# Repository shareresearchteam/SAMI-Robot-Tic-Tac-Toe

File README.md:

# Social Animated Mechanical Interlocutor (SAMI) Robot
The Social Animated Mechanical Interlocutor (SAMI) robot is based on the [Aster](https://www.thingiverse.com/thing:3992150) robot, which is a modified [Poppy](https://www.thingiverse.com/thing:2280067) robot that used MG996R servo motors instead of the much more expensive dynamixels. The SAMI robot has been modified to use the HiWonder HTS serial bus servo motor series in addition to implementing additional features.

## High Level System Capabilities

### Robot
Serial USB connection to PC to send expressions/joint movement commands
Capabilities & DoF:
 1. 8x8 LED matrix eyes, with a bunch of premade expressions (but, as previously mentioned, you can send custom ones, or swap out the eyes entirely
 2. 3 DoF in neck for pan, forward tilt, and side tilt
 3. 2 DoF in chest for forward-backward and side-side lean
 4. 4 DoF for arm (two for the shoulder, one in bicep for arm rotation, one in elbow)
 5. Single tendon gripper for open/close hand (or easy swap in for static or other hand)
 6. 3 DoF for legs (one each hip, knee, ankle)
 7. Mr. Potato Head style swappable headshell parts

### Sensor Box
Serial USB connection sends messages to PC about:
 - Button presses
 - Person presence/movement (ultrasonic + PIR, we’re still fiddling with calibration, but basically to register is someone walks by or comes up to the system)
 - RFID (for specific participant recognition)

### Captions/Speakers/Video/Microphone
Captions are a mini monitor hooked up to the computer, speakers, video and microphone are a webcam or whatever hardware connected to a PC.

### Utilities/etc:
 - JSON-structured animation/behavior/interaction authoring
 - Planning to make some C libraries (with python and c# wrappers) for things like handling serial communication and running the JSON animations/etc
 - Premade eye expressions
 - Premade robot animations/behaviors

## Assembly

## Operation
High level command and operation is managed on a computer system, 
Low level communication with the robot is performed via serial over USB, using the communication packet architecture presented below. 

### Serial Communication Packet Architecture
Each serial packet sent or recieved includes static starting and ending bytes to denote when a packet is complete, and the content between these bytes is our message.
 - Packet start byte char: <
 - Packet end byte char: >

Each message begins with a message topic, which is a single char byte defining the type and structure of content the rest of the message will include. The robot uses one set of message topics, and the sensor box uses a different set of message topics.

The list of existing robot message topics is:
 - J - [Joint Message]()
 - E - [Emote Message]()
 - P - [Power Message]()

The list of existing sensor box message topics is:
 - B - [Button Message]()

These existing message types, corresponding message topics, and remaining content structure are each presented individually below.

#### Joint Message
Joint messages are defined with the message topic byte 'J', followed by the time it should take for the joints to reach the requested position (in seconds) followed then by a list of paired bytes that denote the joint servo id, and the angle

So, a message telling two servos, with ids 1 and 5 to go to 90 degrees in 2 seconds would be 8 bytes and look like:
   <J2190590>

The maximum length of a joint message, if you set all motors, would be:
   start byte + message type + time + (jointID * number of motors) + (jointID * number of motors) + stop byte

For the standard system, which has 21 motors, this would be 46 bytes maximum.

#### Emote Message
Emote messages are defined with the message topic byte 'E', followed by the id for the emote they want to display, as ordered by the NeoEyes library.

So neutral expression would be 4 bytes and look like: <E0>

#### Power Message
Power messages tell us whether to turn the relays on or off, and which relays. We can also send back power messages to the PC if the Arduino automatically cuts a relay because of a motor going over temperature.

Power messages are defined with the message topic byte 'P', followed by a 1 (on) or 0 (off), and which relays to turn on. The relay markers are:
 - T - Neck and torso motor control
 - A - Arms motor control
 - L - Legs motor control
 - E - Everything, aka all of the relays.

The power message is 5, 6, or 7 bytes. A message saying to turn on power to the neck and torso would look like:
   <P1T>

If you wanted to turn off all relays, you could do so either by sending 'E': 
   <P0E>

Or by sending 'TAL' (order invariant, so TLA, ATL, ALT, LTA, or LAT are all acceptable options).
   <P0TAL>

#### Button Message
Button messages send a single integer value corresponding the 0, 1, or 2, which in turn are the first, second, or third button on the sensor box being pressed, beginning from the left hand side when facing towards the front of the box.

## Components/Packages/How TF do I organize this???
Mechanical
Electrical
Arduino Code
C Libraries
JSON behavior files
Audio files + caption text
C# testing/development UI
3D model files
URDF model

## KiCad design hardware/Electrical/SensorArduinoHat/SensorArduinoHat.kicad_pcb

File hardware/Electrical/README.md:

# Aaron Robot Electrical
All of the information for the electrical systems and wiring for the robot.

## Future Improvements
TODO:
 - So much assembly

## Cable Fabrication
There are three power cables that need to be assembled to supply power to the robot. The components and assembly instructions for each are provided below.

For the fork connectors we used [14-16 gauge, #8 fork connectors with heat shrink attached, from wirefy](https://www.amazon.com/dp/B07YBHDBST) and for the spade connectors, we used [10-12 guage, female quick disconnect spade connectors with heat shrink, also from wirefy](https://www.amazon.com/dp/B08BP57G94).

### 12V PCB to Power Supply
This cable assembly connects the 12V power on the motor control PCB to the 12V power supply for the robot.

#### Materials
 - 1x red 14AWG braided wire, 18" length minimum
 - 2x red heat shrink pieces
 - 1x black 14AWG braided wire, 18" length minimum
 - 2x black heat shrink pieces
 - 1x XT-60 female plug
 - 2x fork connector #8, 16-14 gauge opening

#### Assembly
For connecting the wires to the XT-60 connector, you may follow [this](https://www.youtube.com/watch?v=eeDYUymM3XI) short video tutorial.

### 5V PCB to Power Supply
This cable assembly connects the 5V power on the motor control PCB to the 5V power supply for the robot.

#### Materials
 - 1x red 18AWG braided wire, 24" length minimum
 - 2x red heat shrink pieces
 - 1x black 18AWG braided wire, 24" length minimum
 - 2x black heat shrink pieces
 - 1x XT-30 female plug
 - 2x fork connector #8, 22-16 gauge opening

#### Assembly

### 12V Power Supply to Outlet to 5V Power Supply
This cable assembly connects both the 12V power supply and 5V power supply to the power outlet on the back of the chair that takes 120VAC wall power. The 12V supply and 5V supply are at different locations and could use different cable lengths, but for ease of assembly, we use the same lengths of wire for both of them.

#### Materials
 - 2x red 14AWG braided wire, 12" length minimum
 - 3x red heat shrink pieces
 - 2x black 14AWG braided wire, 12" length minimum
 - 3x black heat shrink pieces
 - 2x yellow 14AWG braided wire, 12" length minimum
 - 3x yellow heat shrink pieces
 - 6x fork connector #8, 16-14 gauge opening
 - 3x female spade connector, 12-10 gauge opening

#### Assembly

### Hip Motor to Control PCB JST Cable
For the two motors in the hips, the JST cables that come with the motors will need to be lengthened to reach the motor pcb. You'll need to splice in a 12" length of wire. This can be done by soldering, or with mechanical splice connectors such as [these](https://www.amazon.com/dp/B0DGLJJRZ5).

#### Materials
 - 1x 3 pin JST cable (comes with motor)
 - 1x 3 wire cable, 12" length minimum
 - Solder and heat shrink or [2x mechanical crimp splicers](https://www.amazon.com/dp/B0DGLJJRZ5).

#### Assembly

### Eye Panel Short Cable
This is the short cable combining the two LED array panels for the eyes.

#### Materials
 - 2x 3pin JST XH2.54 connectors
 - 1x 3 wire cable, 4" length (try not to go long)

#### Assembly

### Eye Panel Long Cable
 - 1x 3pin JST XH2.54 connector
 - 1x 3pin JST PH2.0 connector
 - 1x 3 wire cable, ?? length minimum

#### Materials

#### Assembly

### Gripper Cable

#### Materials
 - 1x 3pin JST PH2.0 connector
 - 1x 3pin Dupont female connector
 - 1x 3 wire cable, ?? length minimum

#### Assembly

## Bill of Materials
Currently all in the excel doc one level up

 - Power Supply: 12V, 30A, buck converter down to 6V (Need to check current still)
 - PTC Fuses for each motor: RKEF075-2
 - Relays for each motor group: PR9-5V-200-1A
 - NPN Transistors for each motor group relay controller: BC547CBU-ND
 - Diode between motors and servo: 15SQ100

## Wiring Guide

## Custom PCBs

### Safety Circuitry

#### Motor Current Characteristics

See the motor current characteristics for the arms (without gripper) and legs below. The measured torso nod motor current during operation was seen as a maximum of 0.6A, and the stall current was measured at 1.12A. The measured torso tilt current during operation similarly hit a maximum of 0.6A, but the stall current when held still was 1.99A.

#### Safety Circuit Current Breakdown
We have PTC fuses to protect the servos from melting themselves, and 15A relays so we can cut power to the servos if operation is not currently necessary.

##### Relay Circuits
There are 6 relay groups, broken down for each arm, and leg, as well as the neck and torso. Each relay needs 40mA control current, which becomes 240mA current from the Arduino 5V line. To turn the control circuit on and off, each relay has an individual NPN transistor. These transistors are controlled by a common Arduino pin.

 - Arm Motors: Max Rating: 12.5A, 75W @ 6VDC
    - Chest Shoulder
    - Shoulder
    - Arm Twist
    - Elbow
    - Single Tendon Gripper
 - Leg Motors: Max Rating: 7.5A, 45W @ 6VDC
    - Hip
    - Knee
    - Ankle
    - Hip flexor motor? (add another 2.5A)
 - Head Motors: Max Rating: 7.5A, 45W @ 6VDC
    - Head Twist
    - Head Nod
    - Head Tilt
    - Camera pan motor? (add another 2.5A)
 - Torso Motors: Max Rating: ~6A, 45W @ 7.4VDC
    - Torso Tilt
    - Torso Bow
    - Spine-hip bow point? (adds another ~3A)

## References
 - [Flyback diode example circuit](https://blog.mbedded.ninja/electronics/components/relays/)

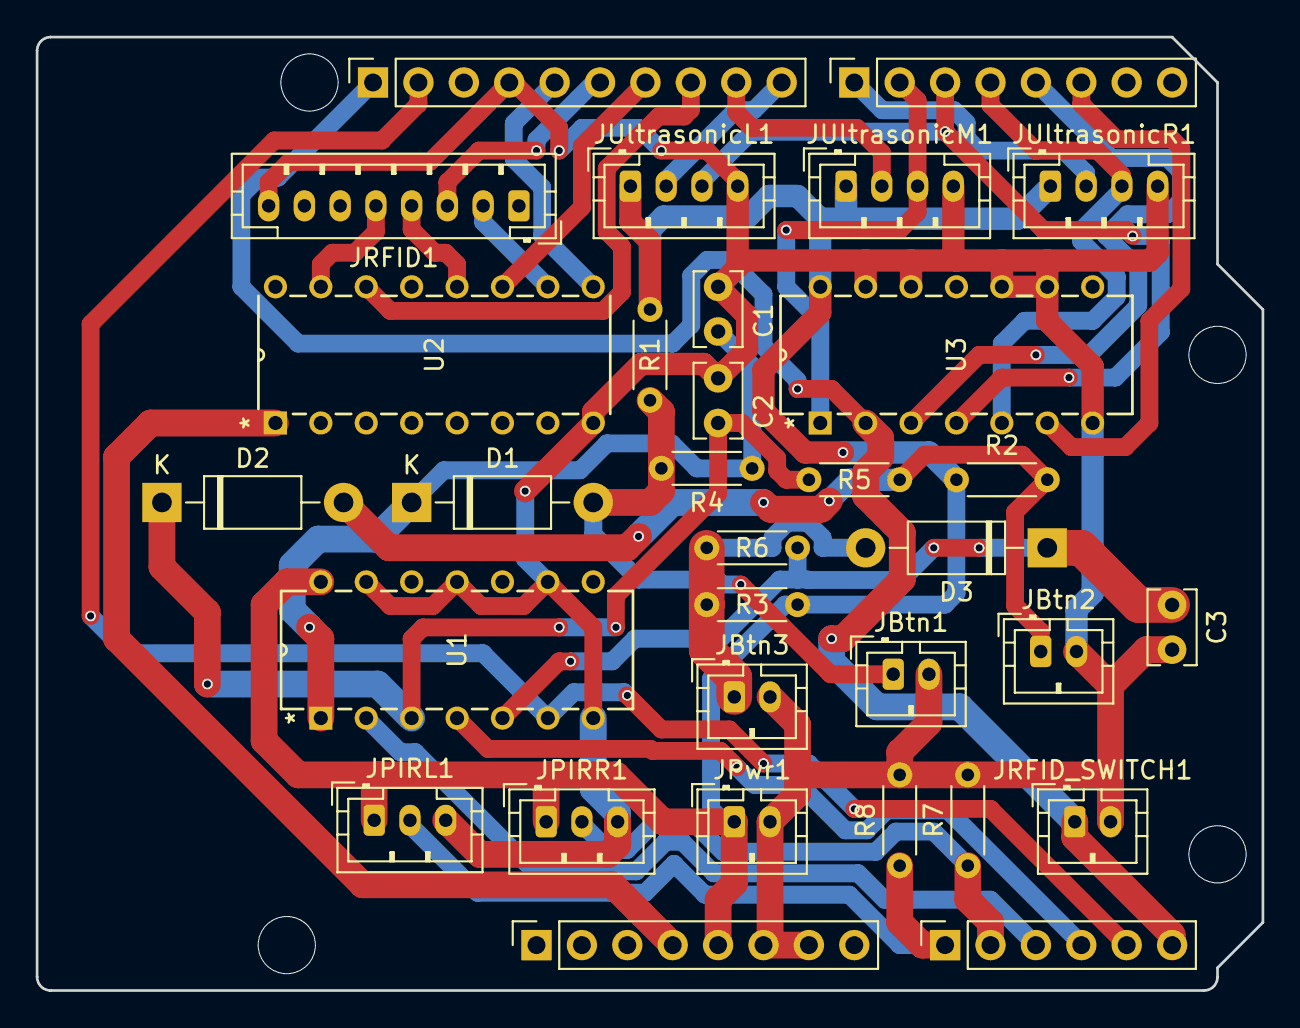
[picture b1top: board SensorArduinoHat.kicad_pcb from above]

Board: 2 copper layers, 68.6 x 53.3 mm, 36 parts (0 on the bottom side), 30 nets.

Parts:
C1, C2, C3: 10uF; C_Rect_L4.0mm_W2.5mm_P2.50mm
D1, D2, D3: 1N4001; D_DO-41_SOD81_P10.16mm_Horizontal
J1: Power; PinSocket_1x08_P2.54mm_Vertical
J2: Digital/PWM; PinSocket_1x10_P2.54mm_Vertical
J3: Analog; PinSocket_1x06_P2.54mm_Vertical
J4: Digital/PWM; PinSocket_1x08_P2.54mm_Vertical
JBtn1, JBtn2, JBtn3: Conn_01x02; JST_PH_B2B-PH-K_1x02_P2.00mm_Vertical
JPIRL1: Conn_01x03; JST_PH_B3B-PH-K_1x03_P2.00mm_Vertical
JPIRR1: Conn_01x03; JST_PH_B3B-PH-K_1x03_P2.00mm_Vertical
JPwr1: Conn_01x02; JST_PH_B2B-PH-K_1x02_P2.00mm_Vertical
JRFID1: Conn_01x08; JST_PH_B8B-PH-K_1x08_P2.00mm_Vertical
JRFID_SWITCH1: Conn_01x02; JST_PH_B2B-PH-K_1x02_P2.00mm_Vertical
JUltrasonicL1: Conn_01x04; JST_PH_B4B-PH-K_1x04_P2.00mm_Vertical
JUltrasonicM1: Conn_01x04; JST_PH_B4B-PH-K_1x04_P2.00mm_Vertical
JUltrasonicR1: Conn_01x04; JST_PH_B4B-PH-K_1x04_P2.00mm_Vertical
MH1, MH2, MH3, MH4: MountingHole_3.2mm
R1, R2, R3, R4, R5, R6, R7, R8: 10k; R_Axial_DIN0204_L3.6mm_D1.6mm_P5.08mm_Horizontal
U1: CD74HC14E; N14
U2: CD4050BE; N16
U3: SN74AHC86N; N14

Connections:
5V: J1.5, JPIRL1.1, JPIRR1.1, JPwr1.1, JUltrasonicL1.1, JUltrasonicM1.1, JUltrasonicR1.1, R1.1, R2.1, R3.1, U1.14 (VCC), U3.14 (VCC)
+3V3: J1.4, U2.1 (VCC)
/2: J4.6, U3.6 (2Y)
/4: J4.4, JUltrasonicR1.3, U3.5 (2B)
/7: J4.1, JUltrasonicR1.2
/8: J2.10, JUltrasonicL1.2
/12: J2.6, JRFID1.3
/13: J2.5, U2.9 (D)
/*3: J4.5, U3.3 (1Y)
/*5: J4.3, JUltrasonicL1.3, U3.4 (2A)
/*6: J4.2, JUltrasonicM1.3, U3.1 (1A)
/*9: J2.9, JUltrasonicM1.2
/*10: J2.8, U2.14 (F)
/*11: J2.7, U2.11 (E)
/A0: J3.1, JPIRL1.2, R8.1
/A1: J3.2, JPIRR1.2, R7.1
/A2: J3.3, U1.2 (1Y)
/A3: J3.4, U1.4 (2Y)
/BtnPin3: J2.2, J3.5, U1.6 (3Y)
/MOSI: JRFID1.4, U2.12 (K=E)
/RFID Card Trigger: J2.1, J3.6, JRFID_SWITCH1.1, U3.2 (1B)
/SCK: JRFID1.2, U2.10 (J=D)
/SSEL: JRFID1.5, U2.15 (L=F)
GND: C1.2, C2.2, C3.2, J1.6, J1.7, J2.4, JBtn1.2, JBtn2.2, JBtn3.2, JPIRL1.3, JPIRR1.3, JPwr1.2, JRFID1.8, JRFID_SWITCH1.2, JUltrasonicL1.4, JUltrasonicM1.4, JUltrasonicR1.4, R7.2, R8.2, U1.7 (GND), U1.9 (4A), U1.11 (5A), U1.13 (6A), U2.8 (VSS), U3.7 (GND), U3.9 (3A), U3.10 (3B), U3.12 (4A), U3.13 (4B)
unnamed: D1.2 (A), JBtn1.1, R1.2, R4.2
unnamed: C1.1, D1.1 (K), R4.1, U1.1 (1A)
unnamed: D2.2 (A), JBtn2.1, R2.2, R5.2
unnamed: C2.1, D2.1 (K), R5.1, U1.3 (2A)
unnamed: D3.2 (A), JBtn3.1, R3.2, R6.2
unnamed: C3.1, D3.1 (K), R6.1, U1.5 (3A)

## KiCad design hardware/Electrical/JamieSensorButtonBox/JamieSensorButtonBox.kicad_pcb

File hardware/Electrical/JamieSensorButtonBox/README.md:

# Sensor Box Circuit
This is the circuitry for the sensor box that sits in front of the system. It is not quite complete, as it will include some external wired components. The control circuit might end up being a custom PCB hat for an Arduino Uno... We'll see.

## To-Do:
 - Complete and confirm full assembly wiring and correct operation
 - Build out BoM
 - Maybe adapt to PCB

## Bill of Materials (BoM)
TODO

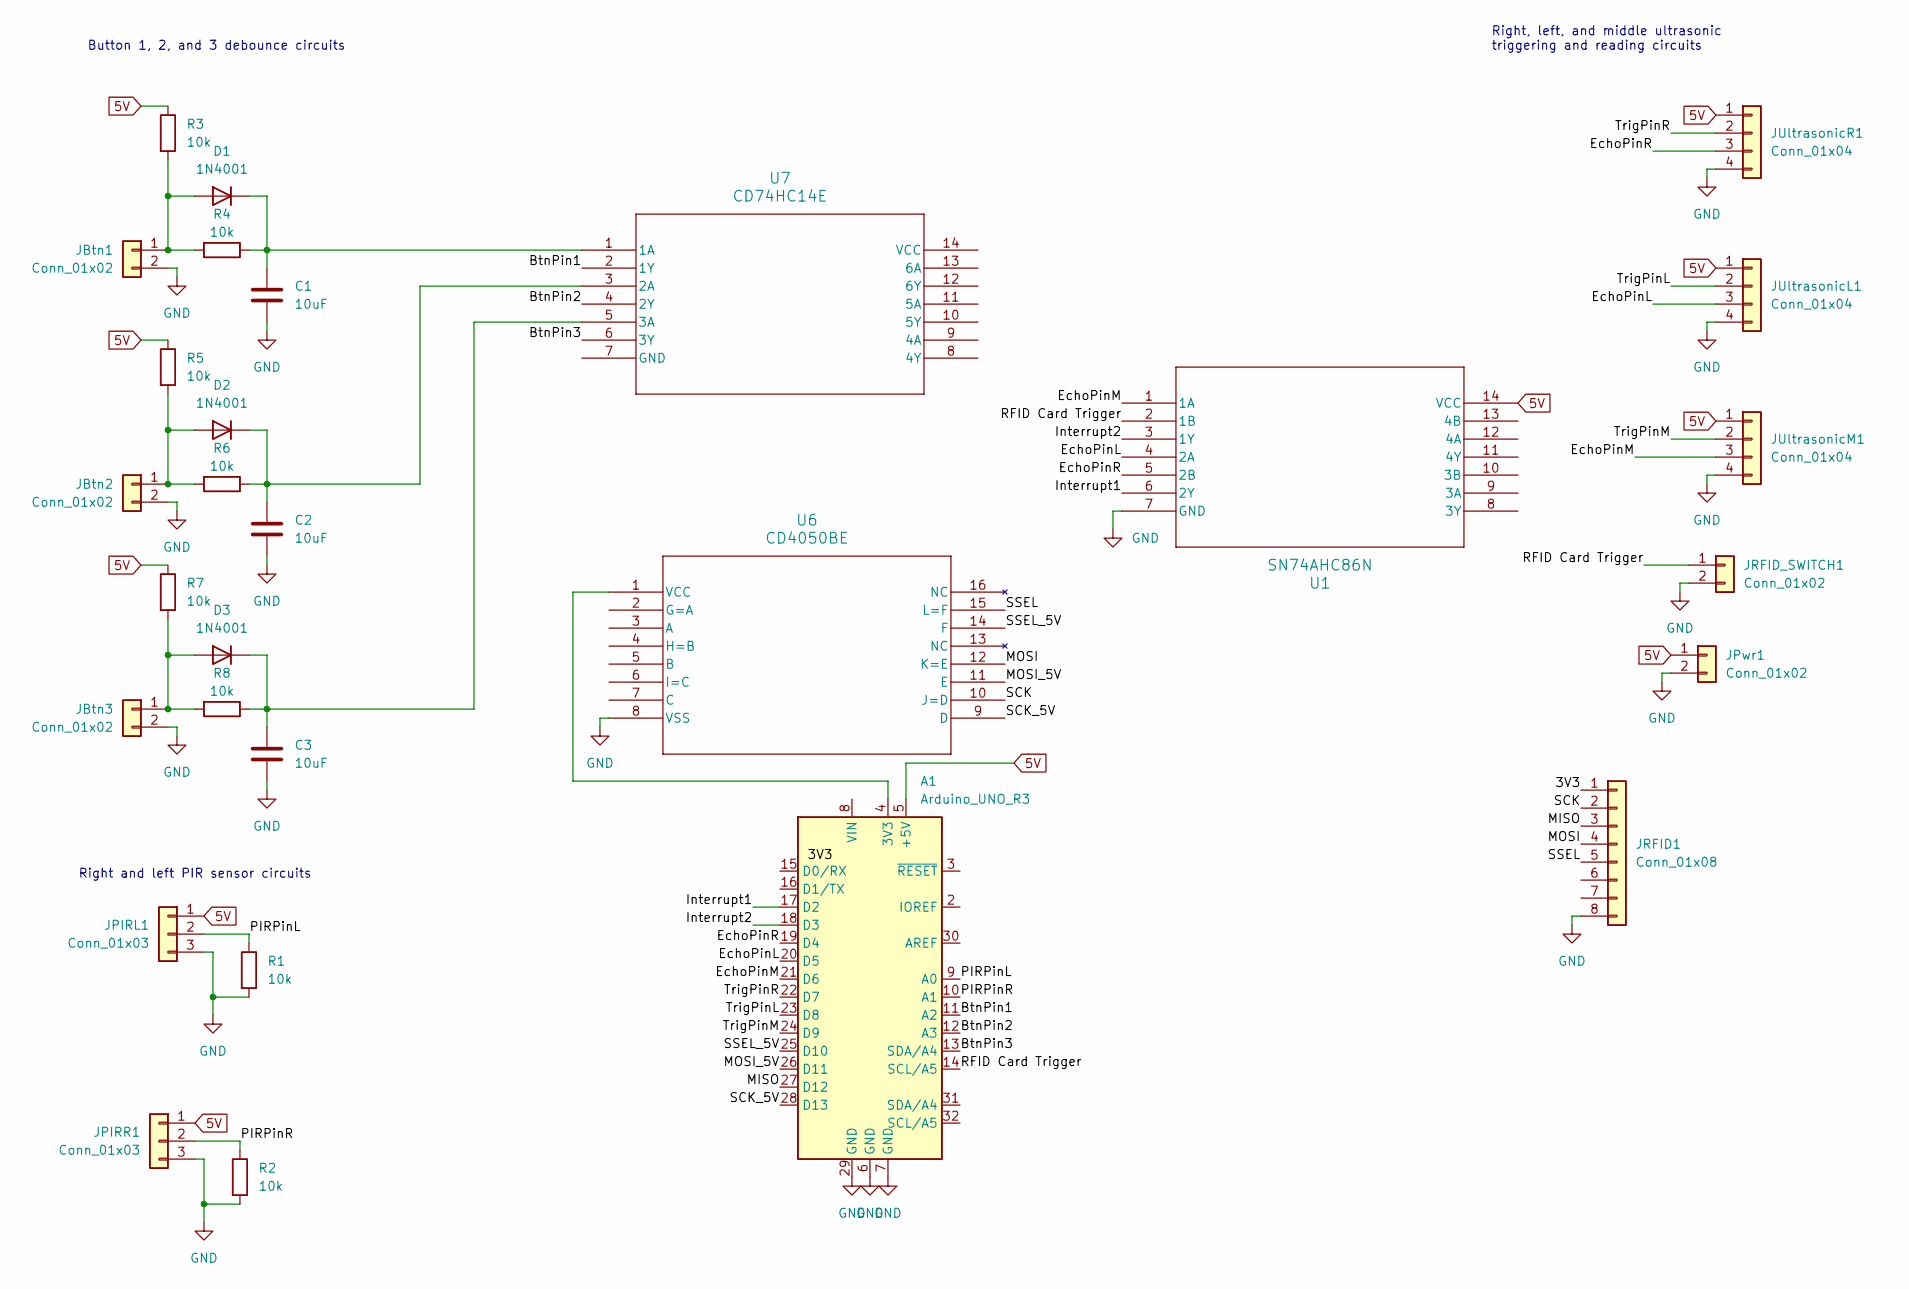
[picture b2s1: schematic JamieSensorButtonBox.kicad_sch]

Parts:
A1: Arduino_UNO_R3
C1, C2, C3: 10uF; C_Rect_L4.0mm_W2.5mm_P2.50mm
D1, D2, D3: 1N4001; D_DO-41_SOD81_P10.16mm_Horizontal
JBtn1, JBtn2, JBtn3: Conn_01x02; JST_PH_B2B-PH-K_1x02_P2.00mm_Vertical
JPIRL1: Conn_01x03; JST_PH_B3B-PH-K_1x03_P2.00mm_Vertical
JPIRR1: Conn_01x03; JST_PH_B3B-PH-K_1x03_P2.00mm_Vertical
JPwr1: Conn_01x02; JST_PH_B2B-PH-K_1x02_P2.00mm_Vertical
JRFID1: Conn_01x08; JST_PH_B8B-PH-K_1x08_P2.00mm_Vertical
JRFID_SWITCH1: Conn_01x02; JST_PH_B2B-PH-K_1x02_P2.00mm_Vertical
JUltrasonicL1: Conn_01x04; JST_PH_B4B-PH-K_1x04_P2.00mm_Vertical
JUltrasonicM1: Conn_01x04; JST_PH_B4B-PH-K_1x04_P2.00mm_Vertical
JUltrasonicR1: Conn_01x04; JST_PH_B4B-PH-K_1x04_P2.00mm_Vertical
R1, R2, R3, R4, R5, R6, R7, R8: 10k; R_Axial_DIN0204_L3.6mm_D1.6mm_P5.08mm_Horizontal
U1: SN74AHC86N; N14
U6: CD4050BE; N16
U7: CD74HC14E; N14

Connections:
5V: A1.5 (+5V), JPIRL1.1, JPIRR1.1, JPwr1.1, JUltrasonicL1.1, JUltrasonicM1.1, JUltrasonicR1.1, R3.1, R5.1, R7.1, U1.14 (VCC)
/3V3: JRFID1.1
/BtnPin1: A1.11 (A2), U7.2 (1Y)
/BtnPin2: A1.12 (A3), U7.4 (2Y)
/BtnPin3: A1.13 (SDA/A4), U7.6 (3Y)
/EchoPinL: A1.20 (D5), JUltrasonicL1.3, U1.4 (2A)
/EchoPinM: A1.21 (D6), JUltrasonicM1.3, U1.1 (1A)
/EchoPinR: A1.19 (D4), JUltrasonicR1.3, U1.5 (2B)
/Interrupt1: A1.17 (D2), U1.6 (2Y)
/Interrupt2: A1.18 (D3), U1.3 (1Y)
/MISO: A1.27 (D12), JRFID1.3
/MOSI: JRFID1.4, U6.12 (K=E)
/MOSI_5V: A1.26 (D11), U6.11 (E)
/PIRPinL: A1.9 (A0), JPIRL1.2, R1.1
/PIRPinR: A1.10 (A1), JPIRR1.2, R2.1
/RFID Card Trigger: A1.14 (SCL/A5), JRFID_SWITCH1.1, U1.2 (1B)
/SCK: JRFID1.2, U6.10 (J=D)
/SCK_5V: A1.28 (D13), U6.9 (D)
/SSEL: JRFID1.5, U6.15 (L=F)
/SSEL_5V: A1.25 (D10), U6.14 (F)
/TrigPinL: A1.23 (D8), JUltrasonicL1.2
/TrigPinM: A1.24 (D9), JUltrasonicM1.2
/TrigPinR: A1.22 (D7), JUltrasonicR1.2
GND: A1.6 (GND), A1.7 (GND), A1.29 (GND), C1.2, C2.2, C3.2, JBtn1.2, JBtn2.2, JBtn3.2, JPIRL1.3, JPIRR1.3, JPwr1.2, JRFID1.8, JRFID_SWITCH1.2, JUltrasonicL1.4, JUltrasonicM1.4, JUltrasonicR1.4, R1.2, R2.2, U1.7 (GND), U6.8 (VSS)
unnamed: A1.4 (3V3), U6.1 (VCC)
unnamed: D1.2 (A), JBtn1.1, R3.2, R4.2
unnamed: C1.1, D1.1 (K), R4.1, U7.1 (1A)
unnamed: D2.2 (A), JBtn2.1, R5.2, R6.2
unnamed: C2.1, D2.1 (K), R6.1, U7.3 (2A)
unnamed: D3.2 (A), JBtn3.1, R7.2, R8.2
unnamed: C3.1, D3.1 (K), R8.1, U7.5 (3A)

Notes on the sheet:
Right, left, and middle ultrasonic triggering and reading circuits
Button 1, 2, and 3 debounce circuits
Right and left PIR sensor circuits

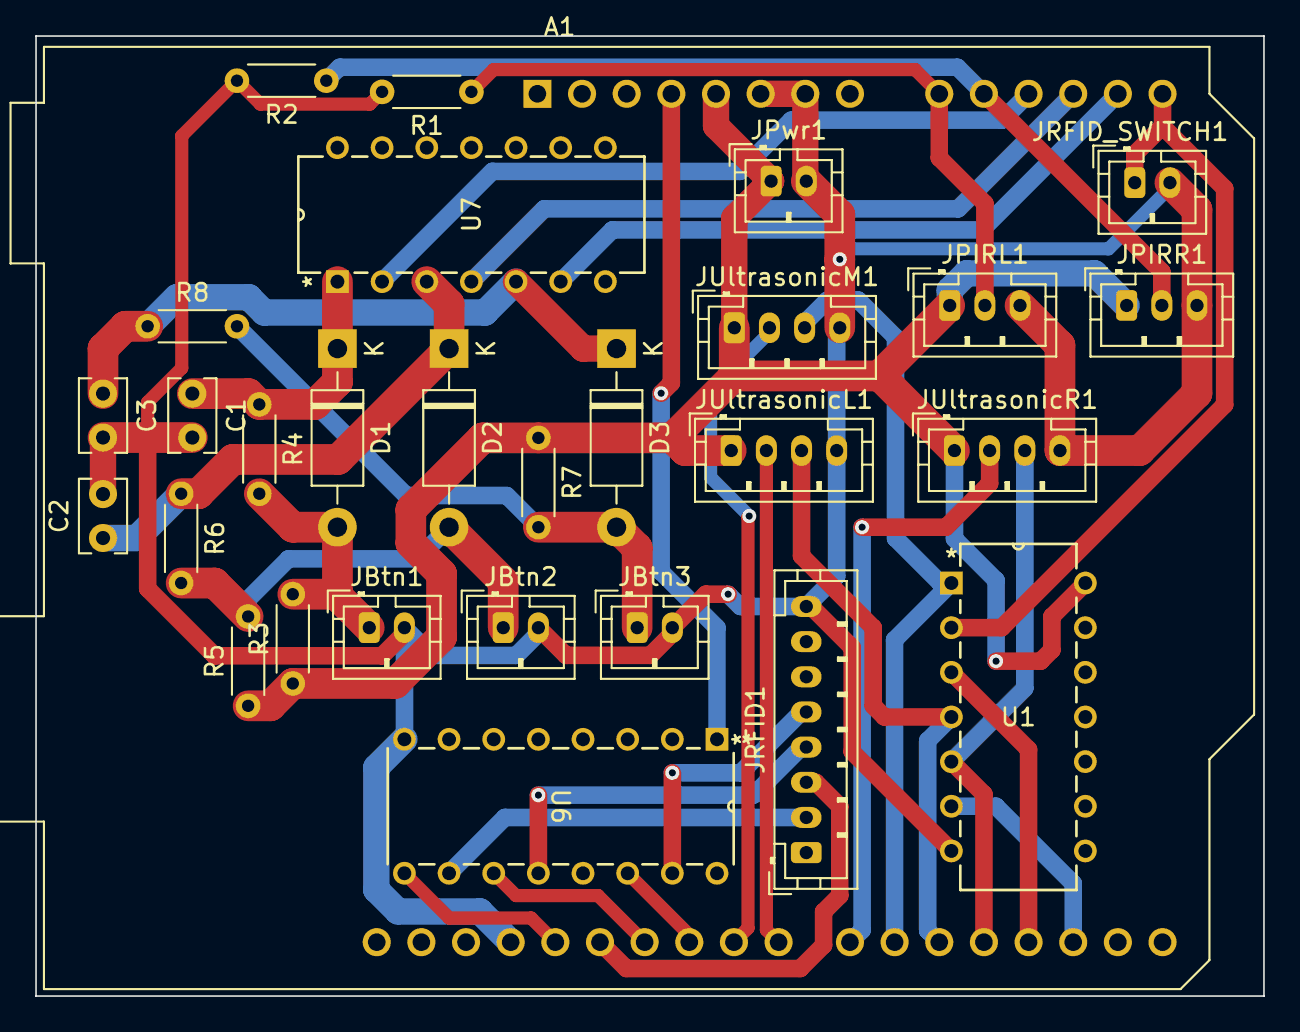
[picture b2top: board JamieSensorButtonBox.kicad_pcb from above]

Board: 2 copper layers, 69.8 x 54.6 mm, 29 parts (0 on the bottom side), 30 nets.

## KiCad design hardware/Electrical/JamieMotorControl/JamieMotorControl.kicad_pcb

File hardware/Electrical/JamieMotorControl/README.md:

# Motor control driver board
Driver board for the servo bus motors. Includes connection for LED eyes, serial control for bus servo motors, and power control for bus servo motors, with mounting spot for microcontroller dev board.

## To-Do Edits for Final PCB
 - Label the relays + transistors for each relay circuit (aka arms relay, legs relay)
 - Fix the big boy diode hole size (Should be like, .082" which is the drill bit size I used the on the drill press, but please fact check me)
 - Transistor spacing (more space between the pads)
 - Q3 trace overlay issue (we're self-shorting lol)
 - Screw holes for the arduino board
 - Zane says we should round our pcb corners lol
 - PCB board name/revision number on solder mask?
 - Making the JST labels end with L or R instead of 1 would make it just a bit easier to read
 - Moving the JST labels out a bit means if we use non-right angle connectors for dumb reasons we can still read the labels
 - The 10k resistor label could be a lil clooooser
 - Having a marker on the jst labels that says which pin is ground would be a bit helpful for confirming which connector direction we need
 - Label for the jsts which pin is signal, pwr, ground (for soldering order safety)
 - The jst left leg vs right leg (and arms) labels actually don't matter because of how the serial is set up, as long as they're on the right relay. (The grippers DO matter tho)
 - Swap the connector for the 5V power to the smaller XT30PW-M connector for protection from user error: https://www.tme.com/us/en-us/details/xt30pw-m/dc-power-connectors/amass/

## Bill of Materials (BoM)
This BoM includes all items necessary to populate this particular PCB. It does not include all items necessary for the entire robot, which can be found [here](../../BoM.md). The parts listed are standalone items you need, as well as a consolidated list of all items you can purchase as a group from [DigiKey](https://www.digikey.com/). 

 - 1x [Mini Arduino ATMEGA2560](https://www.amazon.com/dp/B0D7ZT5M2R), any manufacturer who matches this footprint/pinout will work.
 - 1x [AMASS XT60PW-M Connector](https://www.tme.com/us/en-us/details/xt60pw-m/dc-power-connectors/amass/)
 - 1x [AMASS XT30PW-M Connector](https://www.tme.com/us/en-us/details/xt30pw-m/dc-power-connectors/amass/)
 - 2.54mm pitch female header strips, for connecting the Arduino
 - [DigiKey Part List](../JamieMotorControlBoardDigiKey.csv)

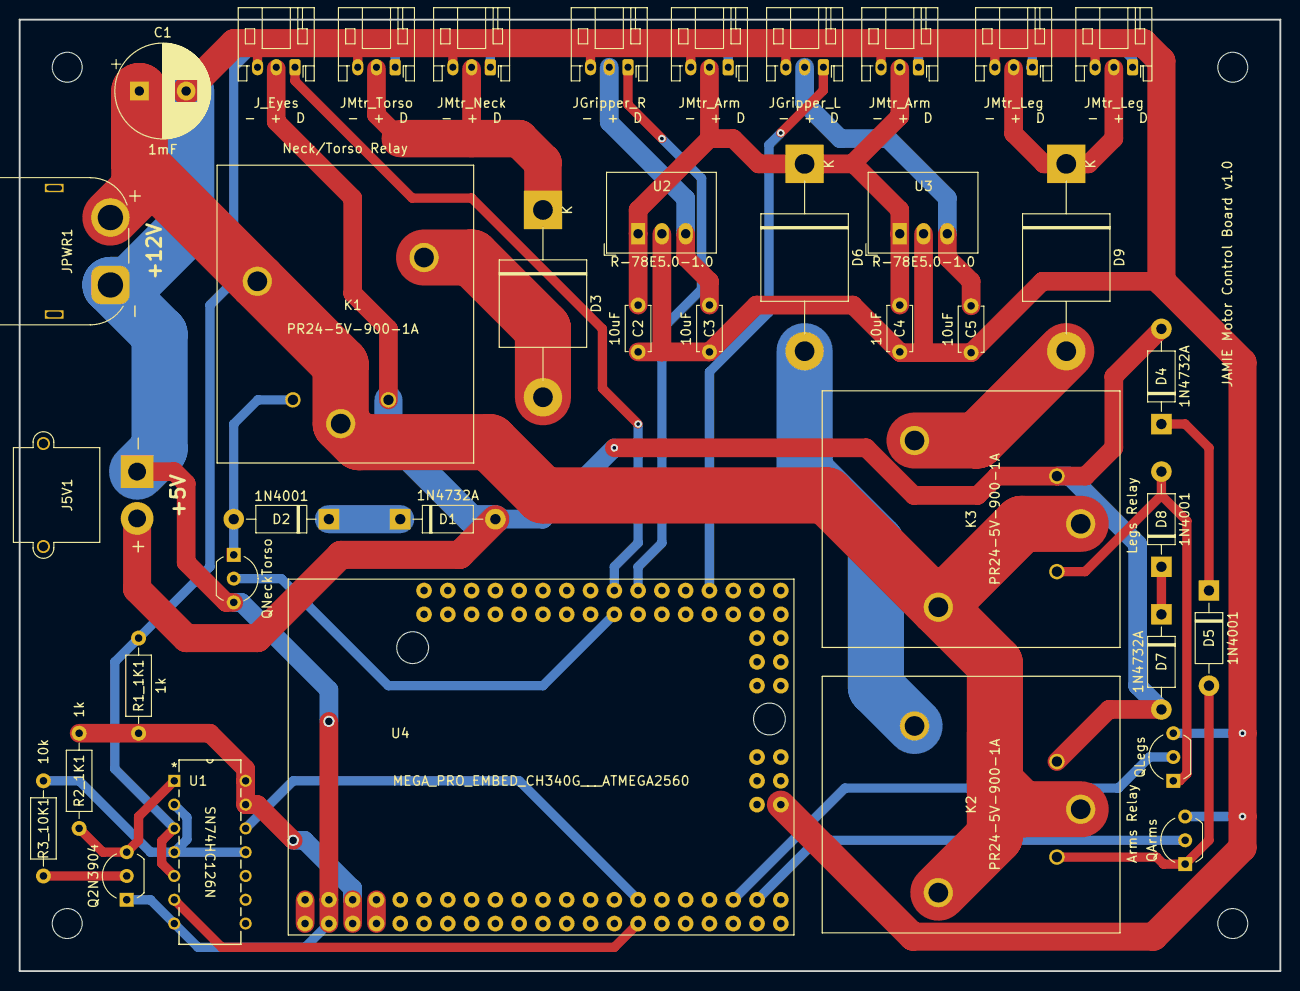
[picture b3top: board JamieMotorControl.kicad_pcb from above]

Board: 2 copper layers, 134.6 x 101.6 mm, 43 parts (0 on the bottom side), 32 nets.

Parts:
C1: 1mF; CP_Radial_D10.0mm_P5.00mm
C2, C3, C4, C5: 10uF; C_Disc_D4.7mm_W2.5mm_P5.00mm
D1, D4, D7: 1N4732A; D_DO-41_SOD81_P10.16mm_Horizontal
D2, D5, D8: 1N4001; D_DO-41_SOD81_P10.16mm_Horizontal
D3, D6, D9: 40SQ045; D_P600_R-7_P20.00mm_Horizontal
H1, H2, H3, H4: MountingHole; MountingHole_3.2mm_M3
J5V1: Conn_01x02; AMASS_XT30PW-M_1x02_P2.50mm_Horizontal
JGripper_L: JST01x03_R; JST_PH_S3B-PH-K_1x03_P2.00mm_Horizontal
JGripper_R: JST01x03_R; JST_PH_S3B-PH-K_1x03_P2.00mm_Horizontal
JMtr_Arm: JST01x03_R; JST_PH_S3B-PH-K_1x03_P2.00mm_Horizontal
JMtr_Arm#2: JST01x03_R; JST_PH_S3B-PH-K_1x03_P2.00mm_Horizontal
JMtr_Leg: JST01x03_R; JST_PH_S3B-PH-K_1x03_P2.00mm_Horizontal
JMtr_Leg#2: JST01x03_R; JST_PH_S3B-PH-K_1x03_P2.00mm_Horizontal
JMtr_Neck: JST01x03_R; JST_PH_S3B-PH-K_1x03_P2.00mm_Horizontal
JMtr_Torso: JST01x03_R; JST_PH_S3B-PH-K_1x03_P2.00mm_Horizontal
JPWR1: Conn_01x02; AMASS_XT60PW-M_1x02_P7.20mm_Horizontal
J_Eyes: JST01x03_R; JST_PH_S3B-PH-K_1x03_P2.00mm_Horizontal
K1, K2, K3: PR24-5V-900-1A; RELAY_PR24-5V-900-1A
Q2N3904: 2N3904; TO-92_Inline_Wide
QArms: BC337; TO-92_Inline_Wide
QLegs: BC337; TO-92_Inline_Wide
QNeckTorso: BC337; TO-92_Inline_Wide
R1_1K1, R2_1K1: 1k; R_Axial_DIN0207_L6.3mm_D2.5mm_P10.16mm_Horizontal
R3_10K1: 10k; R_Axial_DIN0207_L6.3mm_D2.5mm_P10.16mm_Horizontal
U1: SN74HC126N; N14
U2, U3: R-78E5.0-1.0; Converter_DCDC_RECOM_R-78E-0.5_THT
U4: MEGA_PRO_EMBED_CH340G___ATMEGA2560; MODULE_MEGA_PRO_EMBED_CH340G___ATMEGA2560

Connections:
5V: D1.2 (A), D4.2 (A), D7.2 (A), J5V1.2, J_Eyes.2, K1.A1, K2.A1, K3.A1
12V: C1.1, JPWR1.2, K1.COM_1, K1.COM_2, K2.COM_1, K2.COM_2, K3.COM_1, K3.COM_2
/MTR_SIG: JMtr_Arm.1, JMtr_Arm#2.1, JMtr_Leg.1, JMtr_Leg#2.1, JMtr_Neck.1, JMtr_Torso.1, R1_1K1.2, U1.3 (1Y), U1.5 (2A)
/TX_EN: Q2N3904.3 (C), R2_1K1.2, U1.1 (1OE)
/TX_O: R3_10K1.1, U1.2 (1A), U1.4 (2OE), U1.11 (4Y)
ArmsRelay: QArms.2 (B), U4.D28
Eyes: J_Eyes.1, U4.D32
GND: C1.2, C2.2, C3.2, C4.2, C5.2, J5V1.1, JGripper_L.3, JGripper_R.3, JMtr_Arm.3, JMtr_Arm#2.3, JMtr_Leg.3, JMtr_Leg#2.3, JMtr_Neck.3, JMtr_Torso.3, JPWR1.1, J_Eyes.3, Q2N3904.1 (E), QArms.3 (E), QLegs.3 (E), QNeckTorso.3 (E), U1.7 (GND), U2.2 (GND), U3.2 (GND), U4.GND_1 (GND), U4.GND_2 (GND), U4.GND_3 (GND)
HeadTorsoRelay: QNeckTorso.2 (B), U4.D33
LGripper: JGripper_L.1, U4.D40
LegsRelay: QLegs.2 (B), U4.D26
unnamed: D1.1 (K), D2.1 (K)
unnamed: D2.2 (A), K1.A2, QNeckTorso.1 (C)
unnamed: D3.2 (A), K1.NO
unnamed: D3.1 (K), JMtr_Neck.2, JMtr_Torso.2
unnamed: D4.1 (K), D5.1 (K)
unnamed: D5.2 (A), K2.A2, QArms.1 (C)
unnamed: D6.2 (A), K2.NO
unnamed: C2.1, C4.1, D6.1 (K), JMtr_Arm.2, JMtr_Arm#2.2, U2.1 (IN), U3.1 (IN)
unnamed: D7.1 (K), D8.1 (K)
unnamed: D8.2 (A), K3.A2, QLegs.1 (C)
unnamed: D9.2 (A), K3.NO
unnamed: D9.1 (K), JMtr_Leg.2, JMtr_Leg#2.2
unnamed: C5.1, JGripper_L.2, U3.3 (OUT)
unnamed: C3.1, JGripper_R.2, U2.3 (OUT)
unnamed: Q2N3904.2 (B), R3_10K1.2
unnamed: U4.3V3_1 (3V3), U4.3V3_2 (3V3)
unnamed: U4.VIN_1 (VIN), U4.VIN_2 (VIN)
RGripper: JGripper_R.1, U4.D34
RX1: U1.6 (2Y), U4.D19
TX1: U1.12 (4A), U4.D18
VCC: R1_1K1.1, R2_1K1.1, U1.13 (4OE), U1.14 (VCC), U4.5V_1 (5V), U4.5V_2 (5V), U4.5V_3 (5V)

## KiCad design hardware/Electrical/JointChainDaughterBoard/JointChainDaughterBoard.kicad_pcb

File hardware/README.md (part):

# Social Animated Mechanical Interlocutor (SAMI) Robot Hardware
All of the hardware information for the robot system.

 1. [Bill of Materials (BoM)](#bill-of-materials-bom)
 2. [Assembly Instructions](#assembly-instructions)
 3. [Mechanical Information](#mechanical-information)
 4. [Electrical Information](#electrical-information)

## Bill of Materials (BoM)
The below mechanical and electrical BoMs include all components that are assembled into the robot system, and are the minimum hardware requirements necessary to make the system. In addition to this, it is assumed you have a computer to run the higher level system control, with one USB port as a minimum, with an additional USB port for the sensor box, and an HDMI port for the captioning system.

In addition to the above components, as part of the assembly process, it is assumed you have access to standard electrical prototyping equipment such as breadboards and jumper wires, as well as a benchtop power supply or other 12V power source for use during robot assembly.

### Mechanical Bill of Materials
The mechanical BoM includes all of the 3D printed parts, and associated screw pieces (currently in an excel doc for my sanity)

#### Robot 
3D printed so many parts
 - M3 square nuts: 
 - M3 hex nuts: 20
 - M3 lock nuts: 20
 - M3 servo horn screws: 86
 - M3x14 socket cap hex bolts: 8
 - M3x16 socket cap hex bolts: 32
 - M3x20 socket cap hex bolts: 6
 - M3x25 socket cap hex bolts: 4
 - M3x18 flat head countersunk hex bolts: 12
 - Metal servo horns: 19

so, so many screws
Ikea chair
cable ties
diffusion acrylic (optix is what we used)
fishing line (check thickness) and eyelets (for tendon gripper)

#### Sensor Box
3D printer enclosure
3D printed button tops
3D printer button covers
some screws

#### Captioning System
3D printed enclosure
some screws probably

### Electrical Bill of Materials
The electric BoM includes all components necessary for populating all PCBs and sensors, as well as initial assembly. It's currently in an excel doc along with the mechanical bom

#### Robot 
17x HiWonder HTS-20H servos
2x HiWonder HTS-35H servos
2x linear actuator
so much pcb electronics
jst connector cables for the servos
arduino mega 256?
2x adafruit led 8x8 panels
12V power supply
power switch
5V power supply?
more bits idk
usb cable
panel mount usb cable?

##### Optional bits to mount in the robot space:
speakers
microphone
webcam

#### Sensor Box
2x PIR sensor
1x ultrasonic sensor
1x arduino
2x button
rfid thing
more bits
usb cable
panel mount usb cable

#### Captioning System
7" portable monitor (with dimensions matching [this one](https://www.amazon.com/dp/B09MFNLRQQ))
HDMI cable (probably comes with)
usb power cable (probably comes with)

## Assembly Instructions
 1. [Robot Assembly Instructions](#robot-fabrication-and-assembly-instructions)
     1. [3D Printing & Orientations](#3d-printing--orientations)
     2. [Initializing Servo IDs and Positions](#initializing-servo-ids-and-positions)
     3. [Overall Assembly Information]()
     4. [Neck and Torso Assembly](#neck-and-torso-assembly)
     5. [Arm Assembly](#arm-assembly)
     6. [Lower Body Assembly](#lower-body-assembly)
     7. [Final Assembly](#final-assembly)
 2. [Sensor Box Assembly Instructions]()
 3. [Caption Assembly Instructions]()

### Robot Fabrication and Assembly Instructions
This section describes the part fabrication and hardware assembly process for the actual robot.

#### 3D Printing & Orientations
*If using Prusa i3 printers with Prusa Slicer,* all parts should be printed at 0.3mm resolution ("draft quality" on Prusa Slicer), with 15% gyroid infill, and organic supports enabled (where necessary), **except for the chest piece,** which should be printed at 0.2mm resolution, with 15% gyroid infill, and normal grid-style supports instead. Alternatively, the **finger hinges** should be printed using PETG filament with 0% gyroid infill and a brim.

**The hands** used for this robot have been sized down by 42.5% with minimal changes to the bolt holes from the [original prosthetic model](), but the mechanism funtionality remains the same.

Print orientations are shown below for each part, along with the part names that are used throughout this documentation.

##### Headshell

##### Chest and Headshell Panel

##### Head/Neck Connectors and Spine

##### Shoulders and Upper Arms

##### Hands and Lower Arms

##### Finger Hinges

##### Hips and Upper Legs

##### Lower Legs and Feet

#### Initializing Servo IDs and Positions
You will need to communicate with the motors as part of the assembly process. This process can be completed using the completed robot PCB, or the [HiWonder motor debugging board]().

In either case, you will be initializing each motor by connecting and communicating with it individually (*not* chaining the motors). The below initialization instructions assume you are initializing the motors using the robot motor control PCB.

Before assembling the robot, it is necessary to assign unique motor IDs for each joint motor. You can set these IDs with the [SetServoID Arduino code project](../Arduino/SetServoID/) using the motor control PCB for the robot. Any ID numbers may be chosen, but the default configuration file, and these assembly instructions, will use the joint names and IDs as listed in the table below.

|     Joint Name       | ID | Assembly Orientation |
|----------------------|----| -------------------- |
| Head Tilt            | 01 | 125 |
| Head Nod             | 02 | 125 |
| Head Turn            | 03 | 120 |
| Right Chest          | 04 | 125 |
| Right Shoulder       | 05 | 85  |
| Right Bicep          | 06 | 115 |
| Right Elbow          | 07 | 90  |
| Left Chest           | 08 | 115 |
| Left Shoulder        | 09 | 180 |
| Left Bicep           | 10 | 115 |
| Left Elbow           | 11 | 105 |
| Right Hip            | 12 | 90  |
| Right Knee           | 13 | 90  |
| Right Ankle          | 14 | 90  |
| Left Hip             | 15 | 90  |
| Left Knee            | 16 | 90  |
| Left Ankle           | 17 | 90  |
| Torso Tilt           | 18 | 115 |
| Torso Bow            | 19 | 125 |
| Right Gripper        | 20 | 0   |
| Left Gripper         | 21 | 0   |

During assembly of the robot, it will be necessary to set each motor to a known rotation and then assemble the parts to match that orientation. These positions are *not operational home*, but are instead an easy reference position for use in assembly. The robot assembly pose, along with each joint name, motor ID, and the motor angle corresponding to the current pose, are shown in the image below. 

To simplify assembly, the initialization steps for each motor are:

1. Set the motor ID of the servo with the [SetServoID Arduino code project](../Arduino/SetServoID/).
2. Set the motor to it's assembly home position using the [SetServoPosition Arduino code project](../Arduino/SetServoPosition/).
3. While the servo is in the home position, attach the servo horn such that the dimple on the horn is facing towards the servo body as shown below.

5. Cut power to the servo and screw down the aligned horn using the black center screw from the servo accessory bag.

#### Notes On Assembly Process
Some components are sensitive, or could be easily damaged during assembly. To help mitigate this, these notes are provided as important notes to keep in mind during the process.

##### Screwing Threading Plastic and Metal
The entire system is largely assembled with machine screws through 3D printed parts, with either lock nuts or captured square nuts as backing. To aid with alignment and minimize cross-threading the nuts or other components, it's recommended to first screw the machine screws all the way into the 3D printed hole, to thread the plastic and clear any debris from the 3D printing process, before unscrewing the screws, and then assembling the full joint with any nuts, servos, or motor horns screwed in once the plastic holes have been cleared and the screw screws easily into the plastic hole.

Additionally, when screwing to the metal servo horns, it is very easy to misalign your screw and cross thread the screw onto the servo horn. Clearing plastic holes first should allow you to easily hand thread the screw through the plastic into the horn, and simply finish tightening the fully inserted screw down with a hex screwdriver.

##### Servo Horn Alignment
Once a motor has been set to the default position, you can attach the metal horn with the small indent facing towards the motor body (see below image) as a useful visual reference to assist in verifying that the servo does not get misaligned or shifted during the assembly process.

##### Servo JST Cables
The JST cables that come with the servos are a very tight fit into the servo recepticals. We recommend only partially inserting them for initial assembly and testing. These partially inserted connectors will still make electrical contact for continuity testing and motor operation, while still providing more space for pliers to pull the header out without touching the wires themselves. Once operation is confirmed, the connectors can easily be pressed the rest of the way in.

Additionally, despite how tight the connectors are into the recepticals, be very careful when disconnecting them to not pull on the cable wires themselves, as this could damage the individual wires or pull them out of the JST header.

#### Neck and Torso Assembly
When assembling the neck and torso for the robot, it is best to begin with the chest, then spine, and ending with the neck. Throughout this assembly you will need to attach the motors and JST cables onto certain pieces before moving on.

The first step that is **highly** recommended is pre-setting the IDs of all of the Neck and Torso motors before beginning the assembly. 

The HiWonder HTS-20H servos involved in this assembly would be: 
 - Right Chest motor
 - Left Chest motor
 - Head Nod motor
 - Head Tilt motor
 - Head Turn motor 

The two HiWonder HTS-35H servo are also part of this section of the assembly, and are used for the torso motors.
 - Torso Bow motor
 - Torso Tilt motor
 
 All correlated motor IDs are listed above in [Initializing Servo IDs and Positions](#initializing-servo-ids-and-positions), as well as instructions for how to set the IDs and their home positions. It is also recommended that you check the servo horn orientation during this time, following the alignment found in [Servo Horn Alignment](#servo-horn-alignment).

##### Chest Assembly
The chest will require:
 - A P1 philips screwdriver
 - A M2.5 allen key
 - 12x black rubber spacers from the motor package
 - 12x silver servo horn M3 screws
 - 3x JST cables
 - 12 M3 x 16 mm hex screws
 - 8x M3 hex nuts
 - 4x M3 square nuts
 - Motor ID 3
 - Motor ID 4
 - Motor ID 8
 - the Shoulder Connector pieces
 - the chest piece

As recommended in the assembly notes, it is best to pre-thread the screw holes on the 3D printed parts. You should also have already Initialized the motor IDs and home positions with attached servo horns as described in the [initialization instructions](#initializing-servo-ids-and-positions)

Right Shoulder Chest
1. Insert the black rubber spacers into the screw slots for each of motor 4.
2. Insert motor 4 into the right shoulder slot on the chest piece. The servo should be oriented so the servo horn is closer to the back of the chest rather than the front as seen in the side photo below. Note the location of the dimple on the servo horn.

3. Use 4 of the M3x16 screws and 4 of the hex nuts to screw motor 4 to the chest.
4. Use 4 of the silver M3 screws to attach motor 4's servo horn to the righst side Shoulder Connector piece. It should be attached to the horn mount in the middle of the part, and the two sides of the part should be dipping "down" when attached as shown below. 

5. Attach the JST cable to the jst connector on the motor facing the back of the chest piece.

Left Shoulder Chest

6. Insert the black rubber spacers into the screw slots for each of motor 8.
7. Insert motor 8 into the left shoulder slot on the chest piece. The servo should be oriented so the servo horn is closer to the back of the chest rather than the front.
8. Use 4 of the M3x16 screws and 4 of the M3 hex nuts to screw motor 8 to the chest.
9. Use 4 of the silver M3 screws to attach motor 4's servo horn to the righst side Shoulder Connector piece. It should be attached to the horn mount in the middle of the part, and the two sides of the part should be dipping "down" when attached as shown below.

10. Attach the JST cable to the jst connector on the motor facing the back of the chest piece.

With both motors installed and JST cables connected, the chest from behind should look like 

Neck Chest

11. Insert the black rubber spacers into the screw slots for each of motor 3.
12. Insert 2 of the M3 square nuts into the slots in on the inside of the neck of the chest piece, as shown below.

13. Insert motor 3 into the neck of the chest piece. The servo should be oriented so the servo horn is closer to the back of the chest rather than the front.
14. Insert the remaining 2 M3 square nuts into the slots on the back of the neck of the chest piece.
15. Use the remaining 4 M3x16 hex screws to screw down motor 3 to the chest, making sure to screw into the square nuts.
16. Attach the neck piece to the servo horn with 4 silver M3 screws, matching the orientation shown below.

17. Attach the JST cable to the jst connector on the motor facing the back of the chest piece.

<!--The chest assembly will be fairly simple as you’ll be attaching the Right Chest, Left Chest, and Neck motors, then at the end, adding the Chest Connector piece that you just put together. The most difficult part of this assembly will be adding the Chest Connector piece onto the Chest.

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
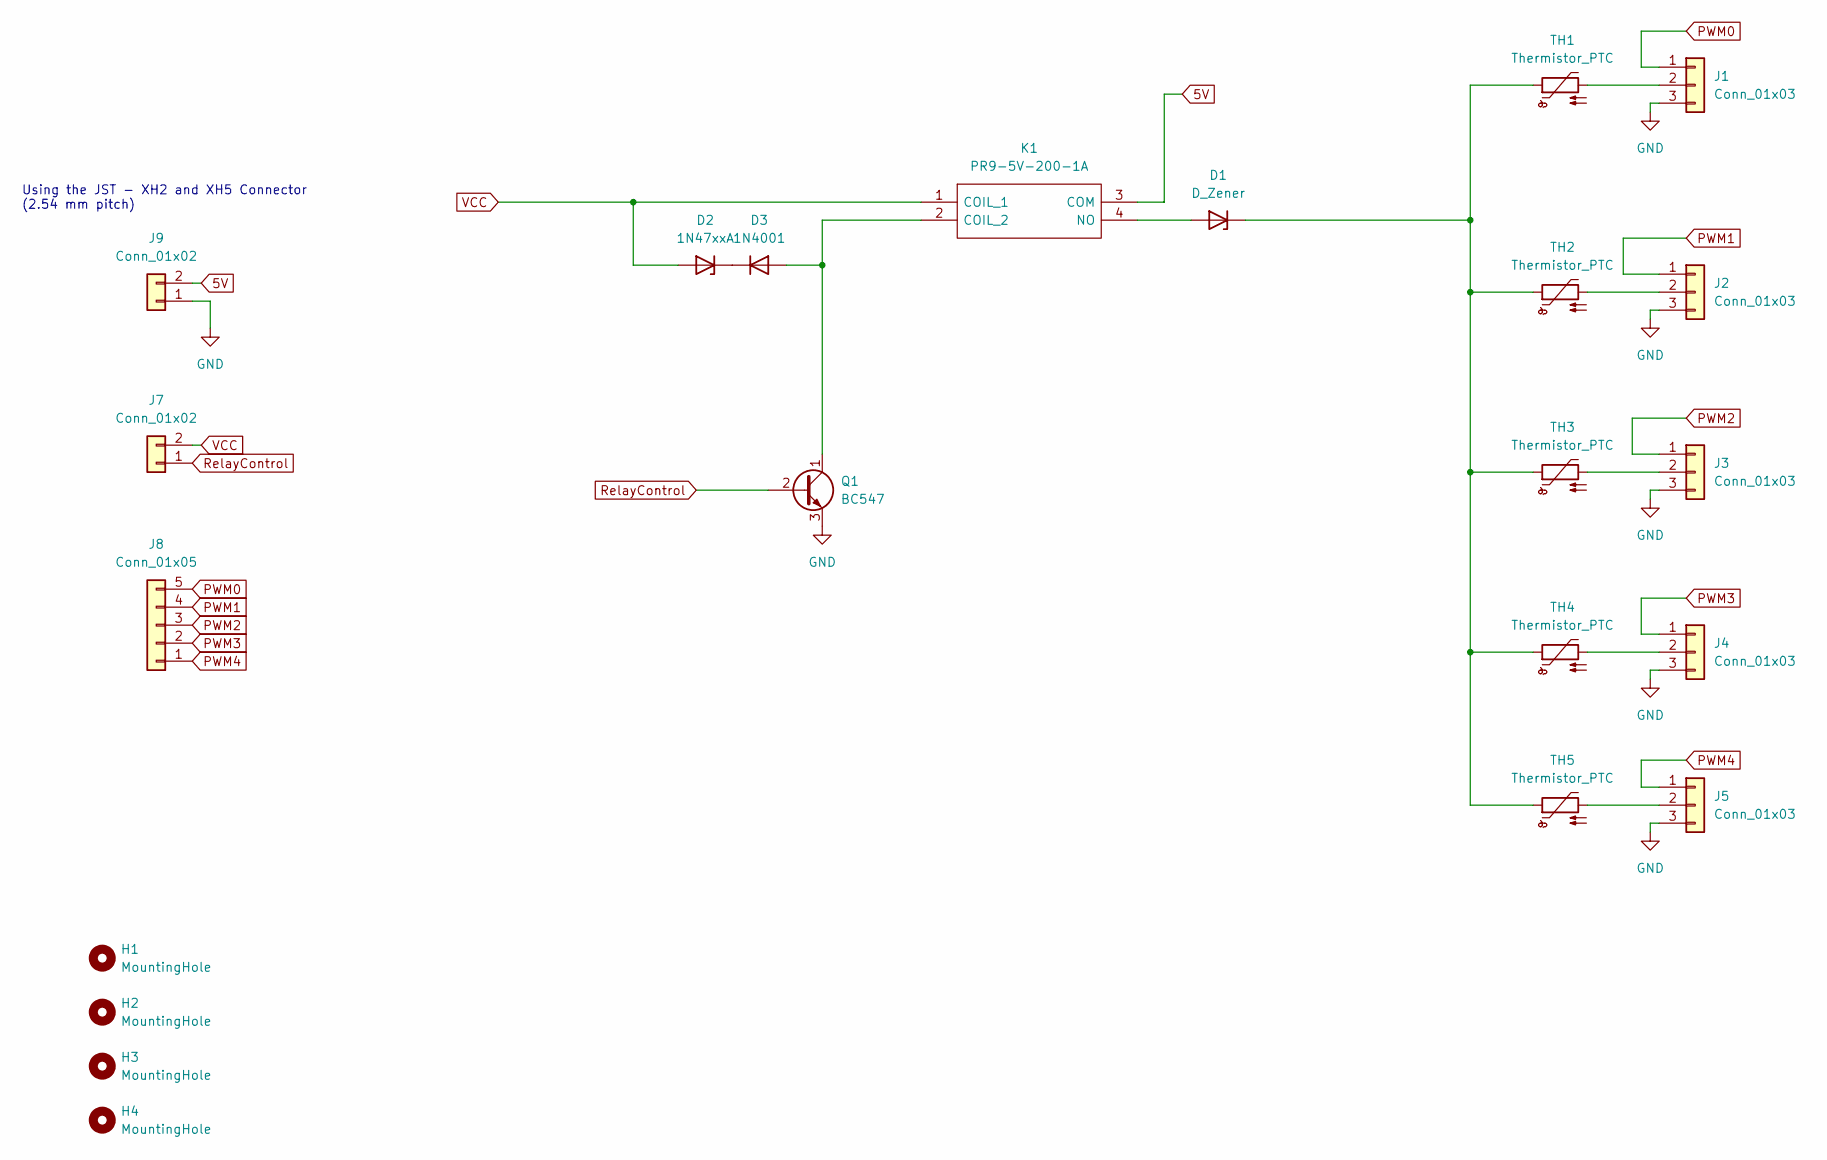
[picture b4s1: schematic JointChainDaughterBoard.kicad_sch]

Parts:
D1: D_Zener; D_P600_R-6_P20.00mm_Horizontal
D2: 1N47xxA; D_DO-41_SOD81_P10.16mm_Horizontal
D3: 1N4001; D_DO-41_SOD81_P10.16mm_Horizontal
H1, H2, H3, H4: MountingHole; MountingHole_3.2mm_M3
J1, J2, J3, J4, J5: Conn_01x03; PinHeader_1x03_P2.54mm_Vertical
J7, J9: Conn_01x02; PinHeader_1x02_P2.54mm_Vertical
J8: Conn_01x05; PinHeader_1x05_P2.54mm_Vertical
K1: PR9-5V-200-1A; PR9 Relay; Mouser Part Number 179-PR9-5V-200-1A
Q1: BC547; TO-92_Inline
TH1, TH2, TH3, TH4, TH5: Thermistor_PTC; R_Box_L8.4mm_W2.5mm_P5.08mm

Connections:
5V: J9.2, K1.3 (COM)
GND: J1.3, J2.3, J3.3, J4.3, J5.3, J9.1, Q1.3 (E)
unnamed: D1.2 (A), K1.4 (NO)
unnamed: D1.1 (K), TH1.1, TH2.1, TH3.1, TH4.1, TH5.1
unnamed: D2.1 (K), D3.1 (K)
unnamed: D3.2 (A), K1.2 (COIL_2), Q1.1 (C)
unnamed: J1.2, TH1.2
unnamed: J2.2, TH2.2
unnamed: J3.2, TH3.2
unnamed: J4.2, TH4.2
unnamed: J5.2, TH5.2
PWM0: J1.1, J8.5
PWM1: J2.1, J8.4
PWM2: J3.1, J8.3
PWM3: J4.1, J8.2
PWM4: J5.1, J8.1
RelayControl: J7.1, Q1.2 (B)
VCC: D2.2 (A), J7.2, K1.1 (COIL_1)

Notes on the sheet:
Using the JST - XH2 and XH5 Connector (2.54 mm pitch)

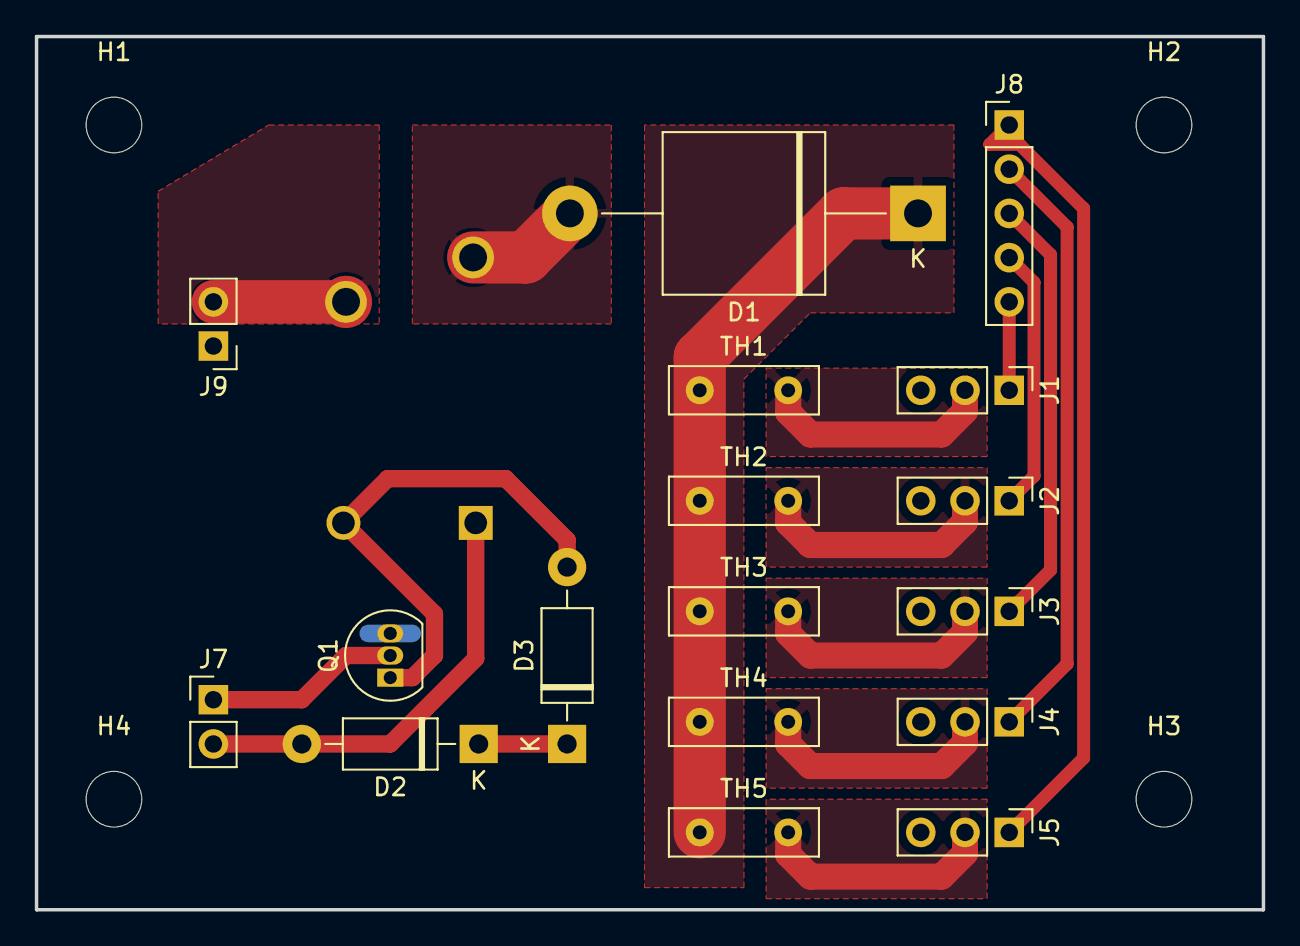
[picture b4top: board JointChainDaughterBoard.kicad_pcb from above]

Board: 2 copper layers, 70.5 x 50.2 mm, 22 parts (1 on the bottom side), 18 nets.
